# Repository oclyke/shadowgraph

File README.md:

# shadowgraph

Firmware for a laser projector built on the [LaserScanner](https://github.com/oclyke/LaserScanner)
hardware: an ESP32 drives two galvanometer axes and an RGB laser from a
time-ordered command stream. Renderers push `goto` / `laser` / `dwell` commands
into a lock-free queue; a hardware-timer-paced consumer task clocks them out to
the DACs.

## Getting Started

```sh
export SHADOWGRAPH_HOST="172.20.10.2"
./play.sh --once tools/svg2scene/examples/chicken.svg

# discover the laser on the network
cargo run --manifest-path tools/artnetctl/Cargo.toml -- --discover --discover-ms 3000 

# send some commands
cargo run --manifest-path tools/artnetctl/Cargo.toml -- --host 172.20.10.2 --mode pattern --intensity 0.25 --fx-morph 0.3 --freq-depth 0.1 --blank-width 0.25 --blank-slide 0.2 --color-cycle 0.1 --color-span 0.2

# go to stream mode for ILDA format control
cargo run --manifest-path tools/artnetctl/Cargo.toml -- --host 172.20.10.2 --mode stream
```

## Hardware

- **MCU:** original ESP32 (Xtensa LX6, dual-core)
- **Galvos:** 2× DAC8871 (16-bit) on SPI2 / HSPI
- **Laser:** 1× DAC80004 (quad 16-bit) on SPI3 / VSPI, channels A/B/C = R/G/B

| Signal | GPIO | | Signal | GPIO |
|--------|------|--|--------|------|
| Galvo MOSI (shared) | IO13 | | Laser MOSI | IO23 |
| Galvo SCLK (shared) | IO14 | | Laser SCLK | IO18 |
| Galvo X — CS / LDAC / RST | IO21 / IO19 / IO22 | | Laser SYNC (CS) | IO26 |
| Galvo Y — CS / LDAC / RST | IO16 / IO15 / IO17 | | Laser LDAC / CLR | IO27 / IO25 |

Pin assignments were traced from the LaserScanner Eagle schematic. The galvo
DACs share one SPI bus with per-device chip selects; the laser DAC is on its own
bus.

## Repository layout

```
shadowgraph/
├── CMakeLists.txt          # top-level ESP-IDF project
├── sdkconfig.defaults      # pins the target to esp32
├── env.sh                  # sets IDF_PATH and sources the ESP-IDF environment
├── main/                   # application entry point (app_main)
├── components/
│   ├── driver_dac8871/     # DAC8871 galvo driver (ESP-IDF v6 SPI/GPIO wrapper)
│   ├── driver_dacx0004/    # DAC80004 laser driver (ESP-IDF v6 SPI/GPIO wrapper)
│   ├── point_ring/         # SPSC lock-free ring of ILDA points
│   ├── laser_engine/       # point ring + fixed-rate timer-ISR DAC consumer
│   ├── point_stream/       # triple-buffered scene store + TCP ILDA receiver
│   ├── artnet_control/     # Art-Net receiver -> render mode + Lissajous settings
│   └── wifi_ap/            # WiFi bring-up (SoftAP or station)
├── tools/
│   ├── svg2scene/          # SVG -> ILDA scene
│   ├── ildaplay/           # stream ILDA frames to the device
│   └── artnetctl/          # Art-Net control: mode toggle + Lissajous settings
└── third-party/github.com/
    ├── espressif/esp-idf           # pinned ESP-IDF v6.0.1
    ├── oclyke/driver-DAC8871       # vendored galvo driver source
    ├── oclyke/driver-DACx0004      # vendored laser driver source
    └── google/googletest           # host-test framework (v1.15.2)
```

Third-party dependencies are vendored as git submodules under
`third-party/github.com/<org>/<repo>`.

## Setup

Clone and fetch the pinned dependencies, then install the toolchain once:

```sh
git clone https://github.com/oclyke/shadowgraph.git
cd shadowgraph

# Fetch all submodules (ESP-IDF and its nested submodules, the DAC drivers,
# and googletest). The ESP-IDF tree is large, so this can take a while.
git submodule update --init --recursive

# Set IDF_PATH and put idf.py on PATH (sources ESP-IDF's export.sh)
source env.sh

# Install the esp32 toolchain
$IDF_PATH/install.sh esp32
```

## Every new shell session

```sh
. env.sh
```

This sets `IDF_PATH` to the pinned ESP-IDF submodule and puts `idf.py` on your
`PATH`.

## Build

```sh
idf.py build
```

## Flash and monitor

```sh
idf.py -p /dev/tty.usbserial-XXXX flash monitor
```

## Configure

```sh
idf.py menuconfig
```

## Clean

```sh
idf.py fullclean
```

## Components

- **driver_dac8871 / driver_dacx0004** — thin ESP-IDF v6 wrappers around the
  vendored DAC driver sources. They supply the SPI/GPIO platform implementation
  (the in-tree `if_imp/esp32` code targets older IDF and is not used).
- **point_ring** — single-producer/single-consumer lock-free ring of
  `laser_point_t`, an ILDA-format point (signed-16-bit X/Y, 8-bit RGB, status).
  Each point is published atomically via a release/acquire handoff.
- **laser_engine** — owns the point ring and the producer API
  (`laser_engine_point` / `laser_engine_points`). A `gptimer` auto-reload alarm
  fires at a fixed sample rate (ILDA-style, default 30 kpps); the ISR pops one
  point per tick, maps its ILDA coordinates to galvo DAC codes and its 8-bit
  color to the laser DAC, and writes them via `isr_spi`. Blanks the laser on
  underrun for safety.
- **point_stream** — triple-buffered DRAM scene store plus a TCP receiver
  (port 7777) that parses standard ILDA off the socket. The renderer loops the
  latest published scene.
- **artnet_control** — an Art-Net (DMX-over-UDP, port 6454) receiver that maps a
  15-channel DMX fixture onto the device's control state: a channel selects the
  render mode (built-in Lissajous **pattern** vs the streamed **scene**), the rest
  tune the pattern's frequency, size, hue, intensity, and morph plus the
  "aliasing" effects — a sliding blank gap, color-as-a-function-of-`t`, and
  per-axis frequency morphing. Drive it from a console, from QLC+/Resolume, or
  from the [`artnetctl`](tools/artnetctl) CLI. Also answers Art-Net **ArtPoll** for
  discovery, so it shows up in any controller's node list (and `artnetctl
  --discover`).

## Control (pattern vs. stream)

The projector starts on its built-in Lissajous and switches to the streamed
scene on command — both selected at runtime over Art-Net, no reflash:

```sh
# don't know the IP? discover it (or use --host auto / shadowgraph.local)
cargo run --manifest-path tools/artnetctl/Cargo.toml -- --discover

# point at the streamed scene, then push frames
cargo run --manifest-path tools/artnetctl/Cargo.toml -- --host auto --mode stream
./play.sh --once tools/svg2scene/examples/chicken.svg

# back to a live pattern (5:4 Lissajous, half size, slow morph)
cargo run --manifest-path tools/artnetctl/Cargo.toml -- \
    --host shadowgraph.local --mode pattern --fx 5 --fy 4 --size 0.5 --morph 0.2
```

The device is reachable three ways without hunting for its DHCP address:
`artnetctl --discover` / `--host auto` (Art-Net **ArtPoll**), or `shadowgraph.local`
(**mDNS** — also works as `--host` for `ildaplay`). See
[`tools/artnetctl`](tools/artnetctl) for the full option list and the DMX channel
map.

## Host unit tests

`point_ring` is pure C and unit-tested on the host with googletest via a
standalone CMake project under `host_test/`:

```sh
# from the repo root
cmake -S components/point_ring/host_test -B components/point_ring/host_test/build
cmake --build components/point_ring/host_test/build
ctest --test-dir components/point_ring/host_test/build --output-on-failure
```

This requires the googletest submodule fetched during setup. `point_stream` and
`artnet_control` carry their own `host_test/` projects too (the Art-Net parser
and DMX decode, the ILDA record decode and triple buffer) — build them the same
way, swapping in the component path.

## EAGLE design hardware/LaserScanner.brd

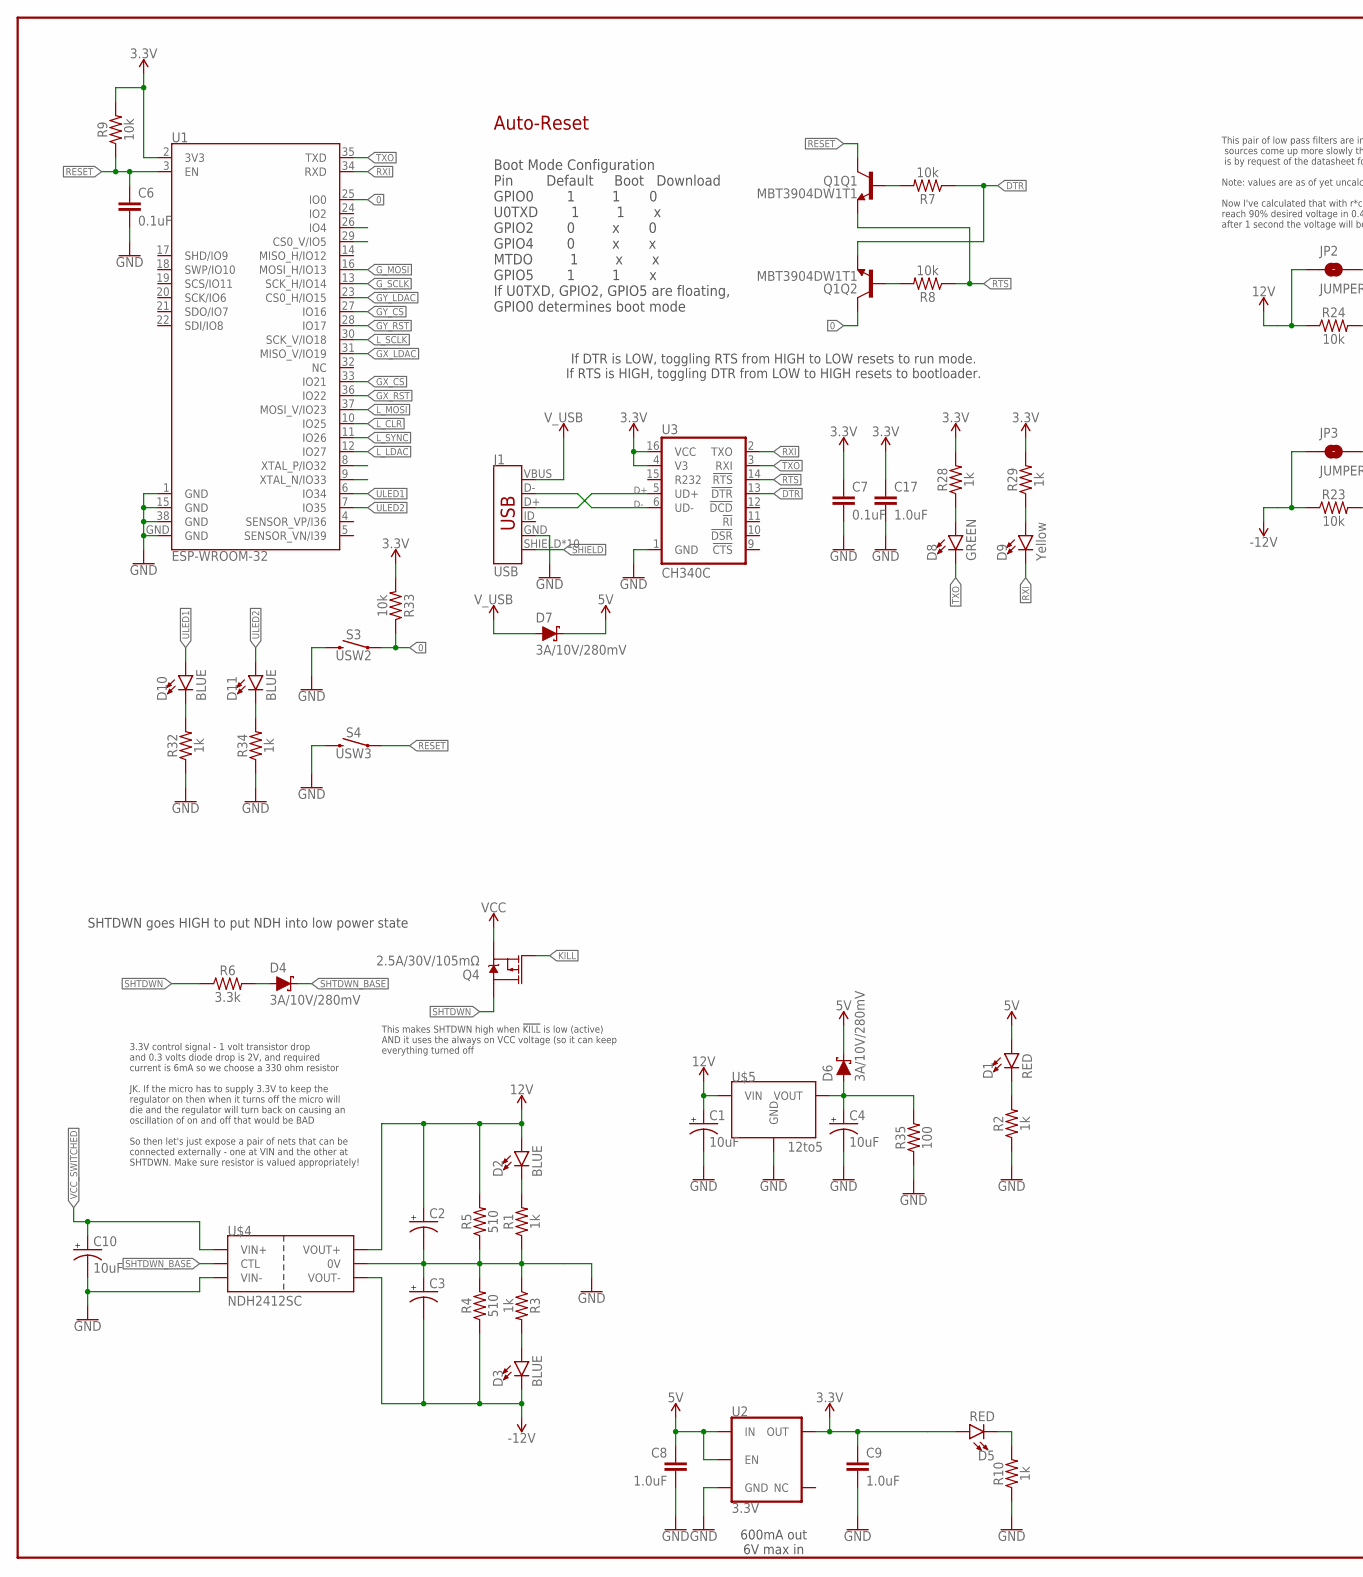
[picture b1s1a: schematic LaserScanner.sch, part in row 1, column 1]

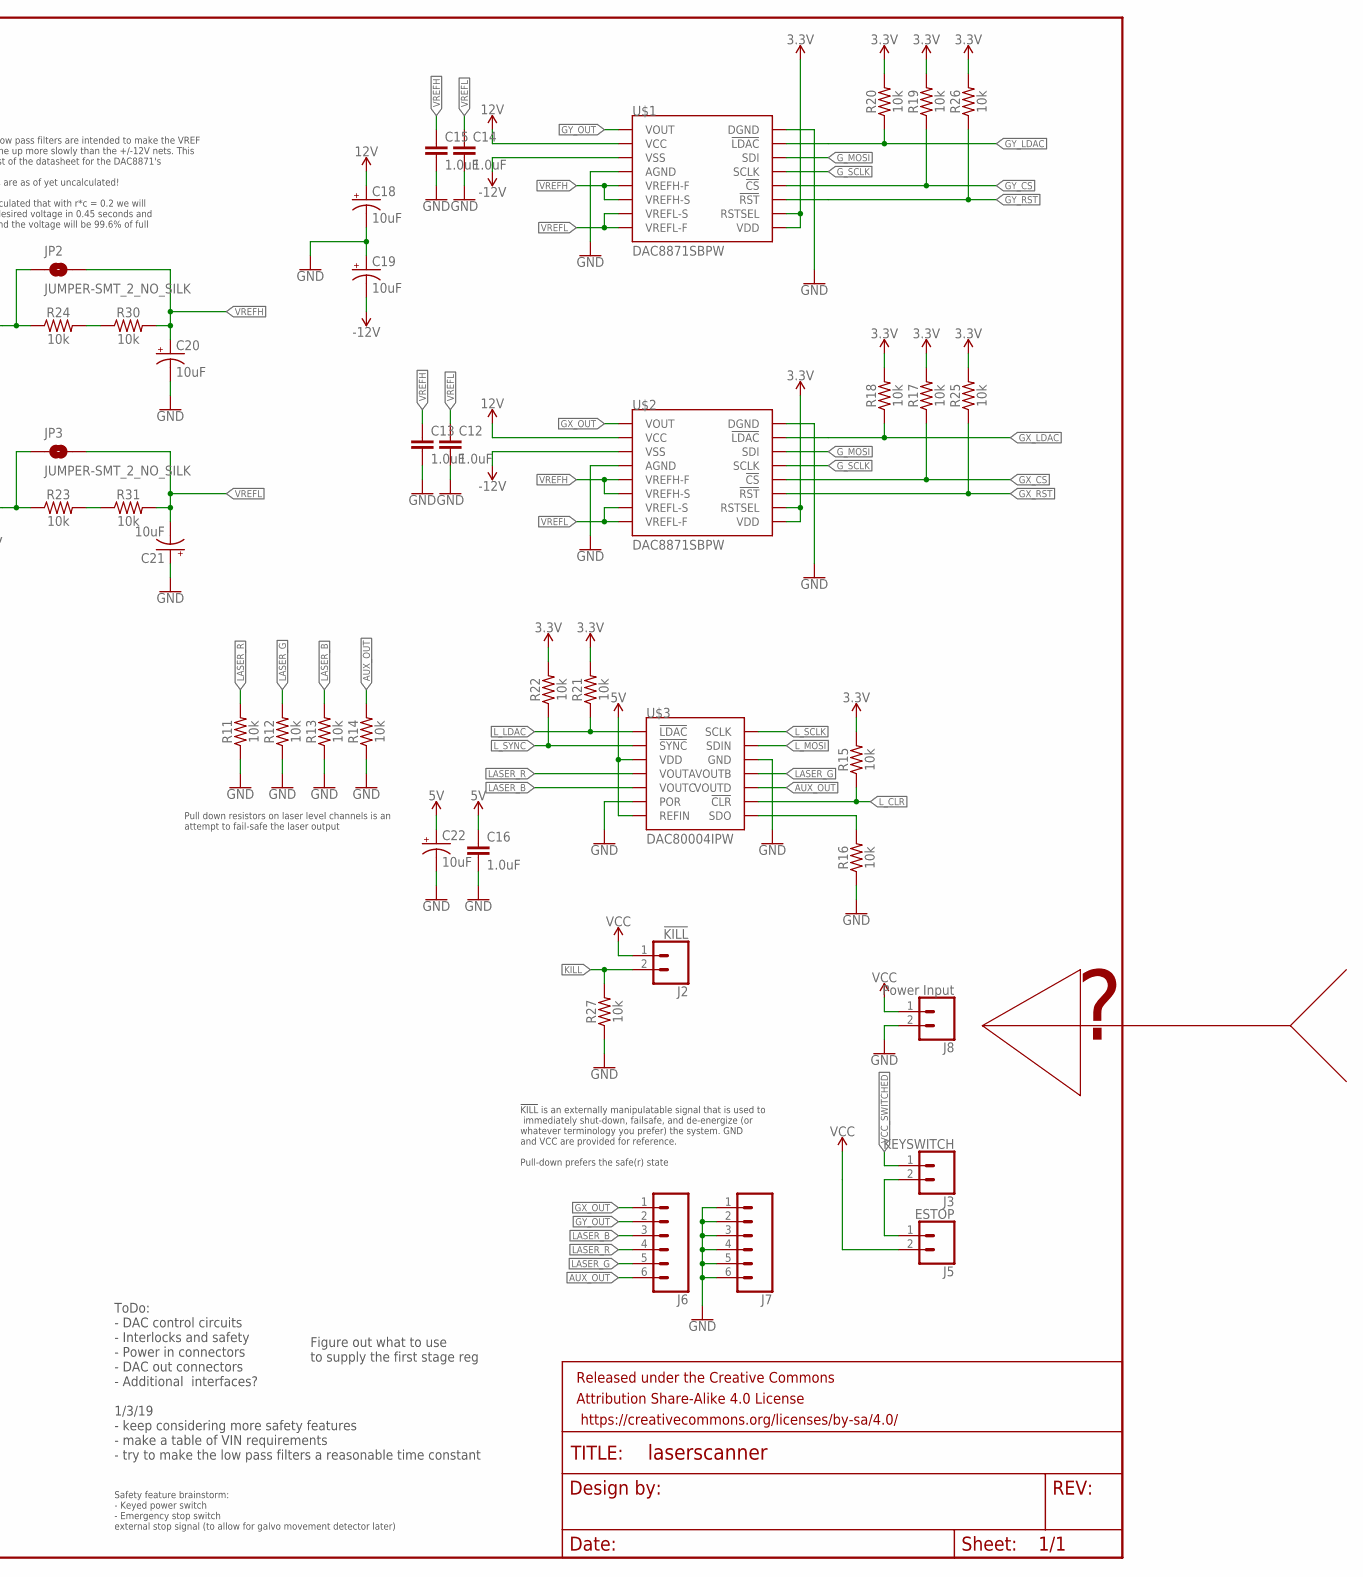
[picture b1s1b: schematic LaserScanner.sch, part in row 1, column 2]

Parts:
C1, C4, C10, C18, C19, C20, C21, C22: 10uF; EIA3216
C2, C3: 47UF-POLAR-PANASONIC_D-50V-20%; PANASONIC_D
C6, C7: 0.1uF; 0603
C8, C9, C12, C13, C14, C15, C16, C17: 1.0uF; 0603
D1, D5: RED; LED-0603
D2, D3, D10, D11: BLUE; LED-0603
D4, D6, D7: 3A/10V/280mV; SOD-323
D8: GREEN; LED-0603
D9: Yellow; LED-0603
FRAME1: FRAME-LEDGER; CREATIVE_COMMONS
J1: USB; USB-MICROB-PTH-MILL
J2: !KILL!; 1X02_NO_SILK
J3: KEYSWITCH; 1X02_NO_SILK
J5: ESTOP; 1X02_NO_SILK
J6, J7: CONN_06NO_SILK_FEMALE_PTH; 1X06_NO_SILK
J8: Power Input; 1X02_NO_SILK
JP2, JP3: JUMPER-SMT_2_NO_SILK; SMT-JUMPER_2_NO_SILK
Q1: MBT3904DW1T1; SC70-6
Q4: 2.5A/30V/105mΩ; SOT23-3
R1, R2, R3, R10, R28, R29, R32, R34: 1k; 0603
R4, R5: 510; 2010
R6: 3.3k; 0603
R7, R8, R9, R11, R12, R13, R14, R15, R16, R17, R18, R19, R20, R21, R22, R23, R24, R25, R26, R27, R30, R31, R33: 10k; 0603
R35: 100; 0603
S3: USW2; TACTILE_SWITCH_SMD_5.2MM
S4: USW3; TACTILE_SWITCH_SMD_5.2MM
U1: ESP-WROOM-32
U2: 3.3V; SOT23-5
U3: CH340C; SO016
U$1, U$2: DAC8871SBPW; TSSOP16
U$3: DAC80004IPW; TSSOP14
U$4: NDH2412SC; NDH
U$5: 12to5; RE-78E

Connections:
0: Q1.6 (C), R33.1, S3.1, S3.2 (1), U1.25 (IO0)
3.3V: C7.1, C9.1, C17.1, D5.A, R9.2, R15.2, R17.2, R18.2, R19.2, R20.2, R21.2, R22.2, R25.2, R26.2, R28.2, R29.2, R33.2, U1.2 (3V3), U2.5 (OUT), U3.4 (V3), U3.16 (VCC), U$1.9 (VDD), U$1.10 (RSTSEL), U$2.9 (VDD), U$2.10 (RSTSEL)
5V: C8.1, C16.1, C22.+, D1.A, D6.C, D7.C, U2.1 (IN), U2.3 (EN), U$3.3 (VDD), U$3.7 (REFIN)
12V: C1.+, C2.+, C18.+, D2.A, JP2.1, R5.2, R24.1, U$1.2 (VCC), U$2.2 (VCC), U$4.6 (VOUT+), U$5.1 (VIN)
!DTR: Q1.1 (E), R7.1, U3.13 (!DTR)
!KILL: J2.2, Q4.1 (G), R27.2
!RTS: Q1.4 (E), R8.1, U3.14 (!RTS)
-12V: C3.-, C19.-, D3.C, JP3.1, R4.1, R23.1, U$1.3 (VSS), U$2.3 (VSS), U$4.9 (VOUT-)
AUX_OUT: J6.6, R14.2, U$3.10 (VOUTD)
D+: J1.D+, U3.5 (UD+)
D-: J1.D-, U3.6 (UD-)
GND: C1.-, C2.-, C3.+, C4.-, C6.2, C7.2, C8.2, C9.2, C10.-, C12.2, C13.2, C14.2, C15.2, C16.2, C17.2, C18.-, C19.+, C20.-, C21.+, C22.-, J1.GND, J7.1, J7.2, J7.3, J7.4, J7.5, J7.6, J8.2, R1.1, R2.1, R3.1, R4.2, R5.1, R10.1, R11.1, R12.1, R13.1, R14.1, R16.1, R27.1, R32.1, R34.1, R35.1, S3.3 (2), S3.4 (2), S4.3 (2), S4.4 (2), U1.1 (GND), U1.15 (GND), U1.38 (GND), U1.GND, U2.2 (GND), U3.1 (GND), U$1.4 (AGND), U$1.16 (DGND), U$2.4 (AGND), U$2.16 (DGND), U$3.6 (POR), U$3.12 (GND), U$4.1 (VIN-), U$4.7 (0V), U$5.2 (GND)
GX_!CS: R17.1, U1.33 (IO21), U$2.12 (!CS)
GX_!LDAC: R18.1, U1.31 (MISO_V/IO19), U$2.15 (!LDAC)
GX_!RST: R25.1, U1.36 (IO22), U$2.11 (!RST)
GX_OUT: J6.1, U$2.1 (VOUT)
GY_!CS: R19.1, U1.27 (IO16), U$1.12 (!CS)
GY_!LDAC: R20.1, U1.23 (CS0_H/IO15), U$1.15 (!LDAC)
GY_!RST: R26.1, U1.28 (IO17), U$1.11 (!RST)
GY_OUT: J6.2, U$1.1 (VOUT)
G_MOSI: U1.16 (MOSI_H/IO13), U$1.14 (SDI), U$2.14 (SDI)
G_SCLK: U1.13 (SCK_H/IO14), U$1.13 (SCLK), U$2.13 (SCLK)
LASER_B: J6.3, R13.2, U$3.5 (VOUTC)
LASER_G: J6.5, R12.2, U$3.11 (VOUTB)
LASER_R: J6.4, R11.2, U$3.4 (VOUTA)
L_!CLR: R15.1, U1.10 (IO25), U$3.9 (!CLR)
L_!LDAC: R21.1, U1.12 (IO27), U$3.1 (!LDAC)
L_!SYNC: R22.1, U1.11 (IO26), U$3.2 (!SYNC)
L_MOSI: U1.37 (MOSI_V/IO23), U$3.13 (SDIN)
L_SCLK: U1.30 (SCK_V/IO18), U$3.14 (SCLK)
unnamed: D1.C, R2.2
unnamed: R16.2, U$3.8 (SDO)
unnamed: D2.C, R1.2
unnamed: D4.A, R6.2
unnamed: D3.A, R3.2
unnamed: D5.C, R10.2
unnamed: C4.+, D6.A, R35.2, U$5.3 (VOUT)
unnamed: J3.2, J5.1
unnamed: Q1.5 (B), R7.2
unnamed: Q1.2 (B), R8.2
unnamed: D8.A, R28.1
unnamed: D9.A, R29.1
unnamed: R24.2, R30.1
unnamed: R23.2, R31.1
unnamed: D10.C, R32.2
unnamed: D11.C, R34.2
RESET: C6.1, Q1.3 (C), R9.1, S4.1, S4.2 (1), U1.3 (EN)
RXI: D9.C, U1.34 (RXD), U3.2 (TXO)
SHIELD: J1.SHIELD, J1.SHIELD2 (SHIELD), J1.SHIELD3 (SHIELD), J1.SHIELD4 (SHIELD), J1.SHIELD5 (SHIELD), J1.SHIELD6 (SHIELD), J1.SHIELD7 (SHIELD), J1.SHIELD8 (SHIELD), J1.SHIELD9 (SHIELD), J1.SHIELD10 (SHIELD)
SHTDWN: Q4.3 (D), R6.1
SHTDWN_BASE: D4.C, U$4.3 (CTL)
TXO: D8.C, U1.35 (TXD), U3.3 (RXI)
ULED1: D10.A, U1.6 (IO34)
ULED2: D11.A, U1.7 (IO35)
VCC: J2.1, J5.2, J8.1, Q4.2 (S)
VCC_SWITCHED: C10.+, J3.1, U$4.2 (VIN+)
VREFH: C13.1, C15.1, C20.+, JP2.2, R30.2, U$1.5 (VREFH-F), U$1.6 (VREFH-S), U$2.5 (VREFH-F), U$2.6 (VREFH-S)
VREFL: C12.1, C14.1, C21.-, JP3.2, R31.2, U$1.7 (VREFL-S), U$1.8 (VREFL-F), U$2.7 (VREFL-S), U$2.8 (VREFL-F)
V_USB: D7.A, J1.VBUS

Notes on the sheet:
Boot Mode Configuration Pin Default Boot Download GPIO0 1 1 0 U0TXD 1 1 x GPIO2 0 x 0 GPIO4 0 x x MTDO 1 x x GPIO5 1 1 x If U0TXD, GPIO2, GPIO5 are floating, GPIO0 determines boot mode
If DTR is LOW, toggling RTS from HIGH to LOW resets to run mode. If RTS is HIGH, toggling DTR from LOW to HIGH resets to bootloader.
Auto-Reset
ToDo: - DAC control circuits - Interlocks and safety - Power in connectors - DAC out connectors - Additional interfaces? 1/3/19 - keep considering more safety features - make a table of VIN requirements - try to make the low pass filters a reasonable time constant
SHTDWN goes HIGH to put NDH into low power state
Figure out what to use to supply the first stage reg
600mA out 6V max in
3.3V control signal - 1 volt transistor drop and 0.3 volts diode drop is 2V, and required current is 6mA so we choose a 330 ohm resistor JK. If the micro has to supply 3.3V to keep the regulator on then when it turns off the micro will die and the regulator will turn back on causing an oscillation 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
Safety feature brainstorm: - Keyed power switch - Emergency stop switch external stop signal (to allow for galvo movement detector later)
Pull down resistors on laser level channels is an attempt to fail-safe the laser output
This pair of low pass filters are intended to make the VREF sources come up more slowly than the +/-12V nets. This is by request of the datasheet for the DAC8871's Note: values are as of yet uncalculated! Now I've calculated that with r*c = 0.2 we will reach 90% desired voltage in 0.45 seconds and 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
This makes SHTDWN high when !KILL! is low (active) AND it uses the always on VCC voltage (so it can keep everything turned off
!KILL! is an externally manipulatable signal that is used to immediately shut-down, failsafe, and de-energize (or whatever terminology you prefer) the system. GND and VCC are provided for reference. Pull-down prefers the safe(r) state

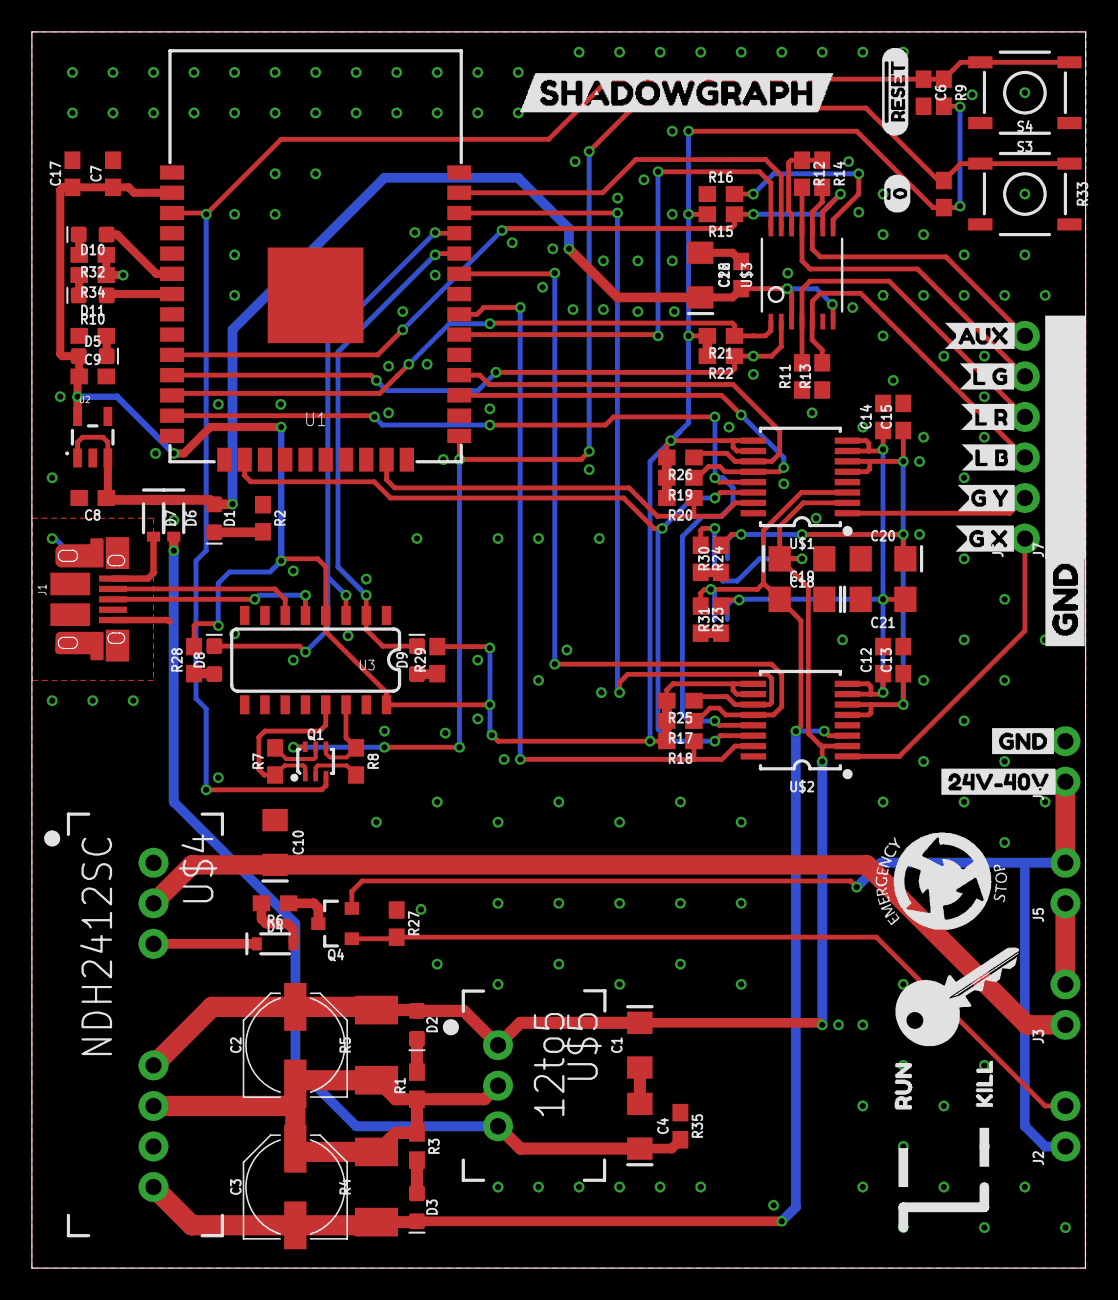
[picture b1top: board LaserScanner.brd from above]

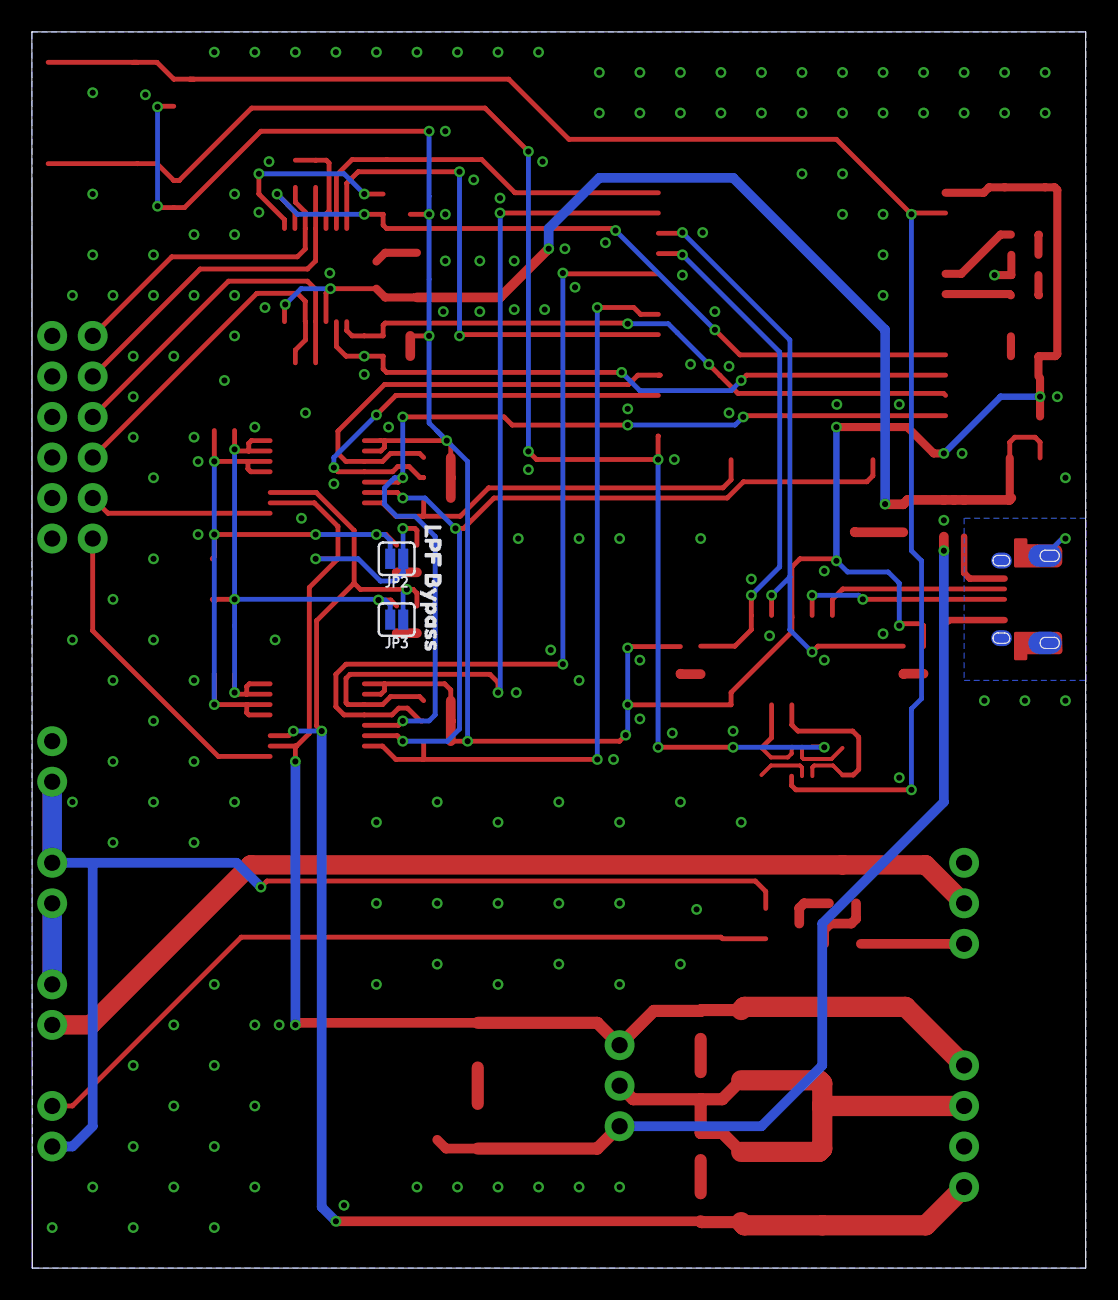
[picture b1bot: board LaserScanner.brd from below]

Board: 2 copper layers, 66.0 x 77.5 mm, 105 parts (3 on the bottom side), 59 nets.

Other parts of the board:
U$6: KEY#PNG
U$7: E#STOP#JPG
U$8: 24V#40V3
U$9: GND0
U$10: GND1
U$11: KILL11
U$12: RUN10
U$13: #RESET14
U$14: #013
U$15: AUX4
U$16: G_X14
U$17: G_Y13
U$18: L_B12
U$19: LPF_BYPASS12
U$20: L_R14
U$21: L_G10
U$22: SHADOWGRAPH15

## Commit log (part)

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2026-06-09 add esp idf
2026-06-09 add hello world
2026-06-09 add DAC driver submodules
2026-06-09 wrap DAC drivers as components
2026-06-09 wire up DACs to hardware
2026-06-10 solve upload problem w/ lower baud rate
2026-06-10 ignore cache
2026-06-10 add test code
2026-06-10 resolve dac8871 spi mode issue
2026-06-10 add googletest
2026-06-10 add laser engine components
2026-06-10 demo laser color control
2026-06-10 add lissajous movement
2026-06-10 separate color and movement times for smoother movement
2026-06-10 ignore claude workspace
2026-06-10 add wifi AP
2026-06-11 ignore pycache
2026-06-11 add preliminary UDP source
2026-06-12 initial svg pipeline
2026-06-12 improve svg2scene
2026-06-12 ignore output
2026-06-15 disable wifi during testing
2026-06-15 phase 0
2026-06-16 phase 1
2026-06-16 phase 2
2026-06-16 upgrade test svg
2026-06-16 improvements
2026-06-16 fix tests
2026-06-16 document next steps
2026-06-16 do euler optimization?
2026-06-16 improve laser driver performance with smaller integer math
2026-06-16 unify comments
2026-06-16 check for limits saturation
2026-06-16 commit saturated max speed
2026-06-16 fix for low-speed lasers (they lag real time)
2026-06-16 add wifi sta mode
2026-06-16 add UDP echo demo
2026-06-16 add bicycle.svg
2026-06-16 add chicken.svg
2026-06-16 add hair.svg
2026-06-16 add frame streaming to firmware
2026-06-16 add frame streaming tool
2026-06-16 wire up svg2scene with frame_send
2026-06-16 support curve drawing (#3)
    Add curve drawing support.
2026-06-16 ignore osx
2026-06-16 add original hardware design
2026-06-16 hardware (#4)
    * ignore osx
    * add original hardware design
2026-06-23 ILDA style control
2026-06-23 increase clock speed
2026-06-23 improve perf with ram-only render
2026-06-23 ILDA streaming
2026-06-23 add ilda tooling
2026-06-23 tolerant to play ILDA files
2026-06-23 add home.svg
2026-06-23 artnet control basics
2026-06-23 artnet control
2026-06-23 fancy test pattern
2026-06-23 switch to AP
2026-06-29 add dobby
2026-06-29 add png trace tool
2026-06-29 attempt color quantization

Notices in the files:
parts and their libraries:
SparkFun-Capacitors: Licensing: Creative Commons ShareAlike 4.0 International - https://creativecommons.org/licenses/by-sa/4.0
SparkFun-Aesthetics: Released under the Creative Commons Attribution Share-Alike 4.0 License
SparkFun-Aesthetics: https://creativecommons.org/licenses/by-sa/4.0
